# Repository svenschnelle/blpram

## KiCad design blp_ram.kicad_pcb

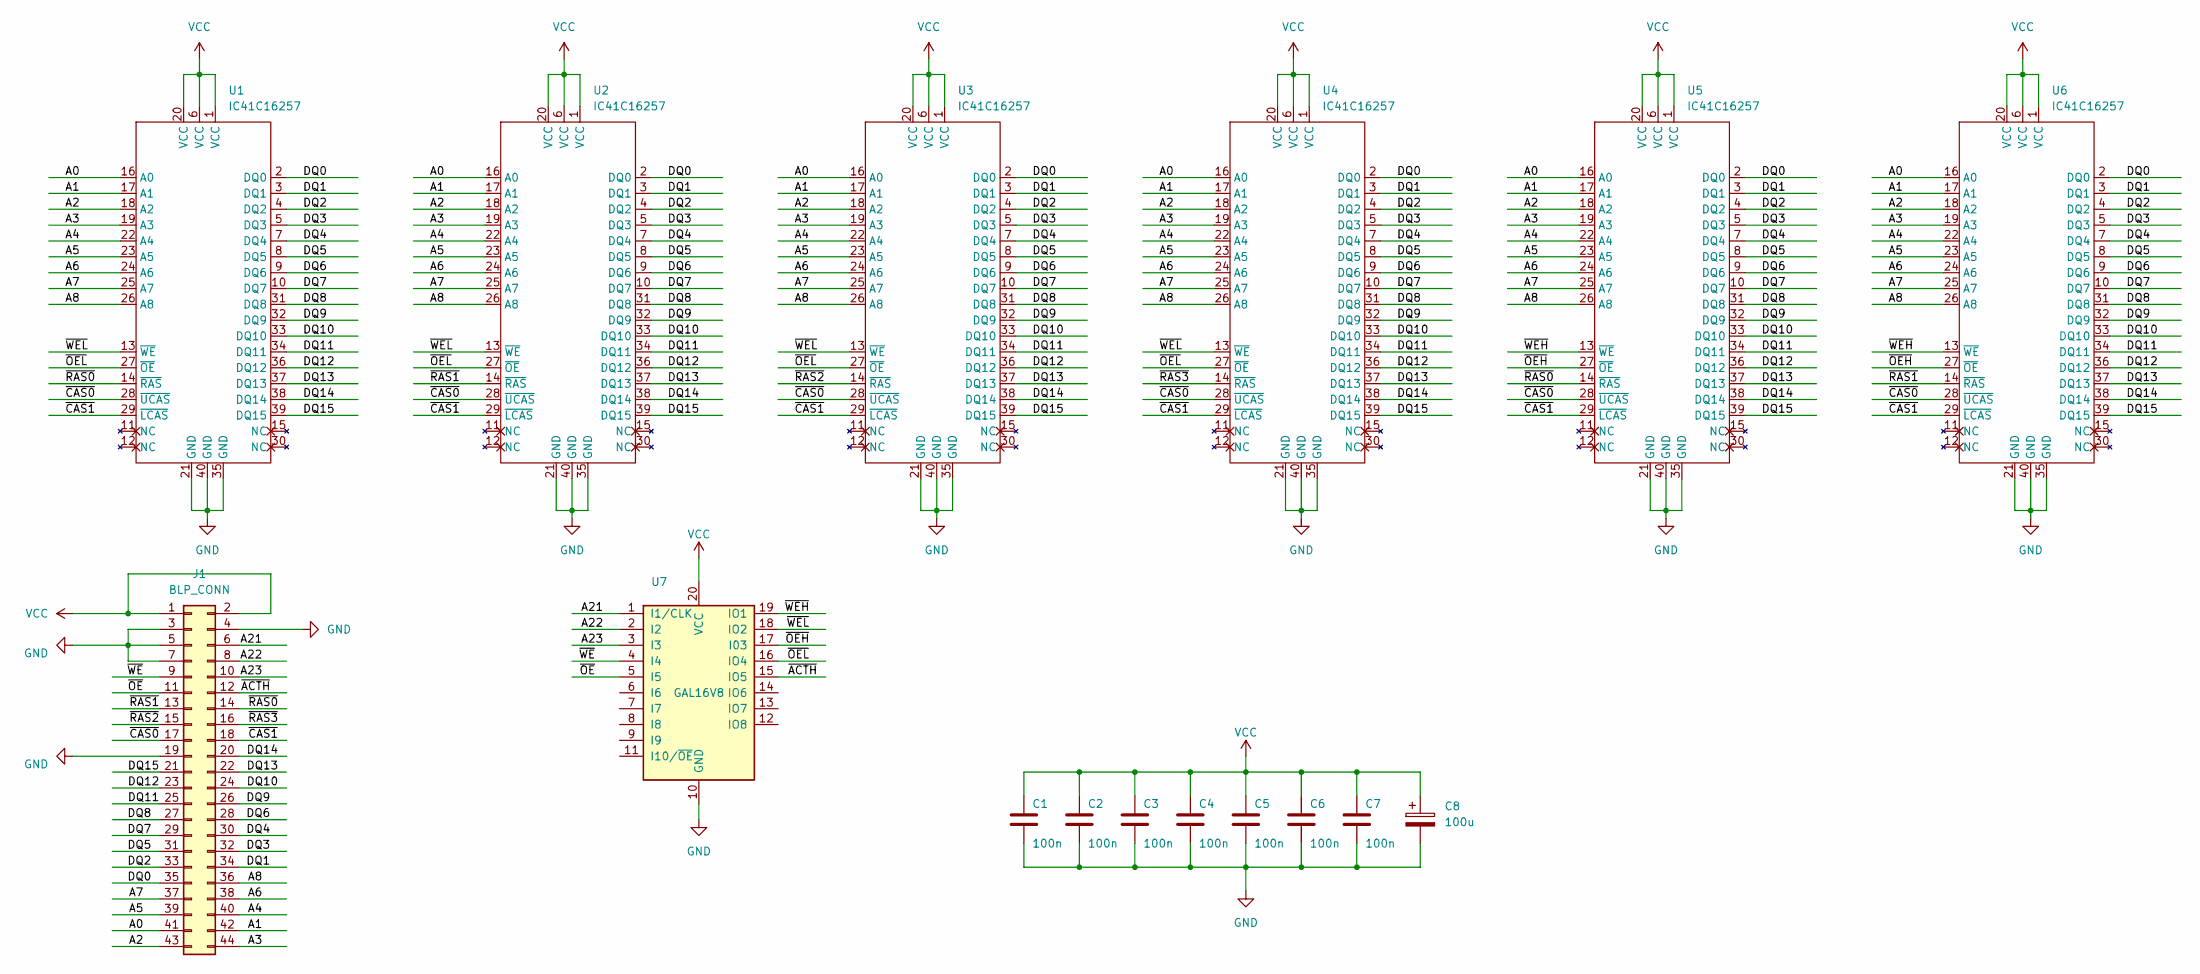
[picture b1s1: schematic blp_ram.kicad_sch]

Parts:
C1, C2, C3, C4, C5, C6, C7: 100n; R_1206_3216Metric_Pad1.30x1.75mm_HandSolder
C8: 100u; CP_Radial_D6.3mm_P2.50mm
J1: BLP_CONN; PinHeader_2x22_P2.54mm_Vertical
U1, U2, U3, U4, U5, U6: IC41C16257; SOJ-40
U7: GAL16V8; DIP-20_W7.62mm

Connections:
/A0: J1.41, U1.16 (A0), U2.16 (A0), U3.16 (A0), U4.16 (A0), U5.16 (A0), U6.16 (A0)
/A1: J1.42, U1.17 (A1), U2.17 (A1), U3.17 (A1), U4.17 (A1), U5.17 (A1), U6.17 (A1)
/A2: J1.43, U1.18 (A2), U2.18 (A2), U3.18 (A2), U4.18 (A2), U5.18 (A2), U6.18 (A2)
/A3: J1.44, U1.19 (A3), U2.19 (A3), U3.19 (A3), U4.19 (A3), U5.19 (A3), U6.19 (A3)
/A4: J1.40, U1.22 (A4), U2.22 (A4), U3.22 (A4), U4.22 (A4), U5.22 (A4), U6.22 (A4)
/A5: J1.39, U1.23 (A5), U2.23 (A5), U3.23 (A5), U4.23 (A5), U5.23 (A5), U6.23 (A5)
/A6: J1.38, U1.24 (A6), U2.24 (A6), U3.24 (A6), U4.24 (A6), U5.24 (A6), U6.24 (A6)
/A7: J1.37, U1.25 (A7), U2.25 (A7), U3.25 (A7), U4.25 (A7), U5.25 (A7), U6.25 (A7)
/A8: J1.36, U1.26 (A8), U2.26 (A8), U3.26 (A8), U4.26 (A8), U5.26 (A8), U6.26 (A8)
/A21: J1.6, U7.1 (I1/CLK)
/A22: J1.8, U7.2 (I2)
/A23: J1.10, U7.3 (I3)
/DQ0: J1.35, U1.2 (DQ0), U2.2 (DQ0), U3.2 (DQ0), U4.2 (DQ0), U5.2 (DQ0), U6.2 (DQ0)
/DQ1: J1.34, U1.3 (DQ1), U2.3 (DQ1), U3.3 (DQ1), U4.3 (DQ1), U5.3 (DQ1), U6.3 (DQ1)
/DQ2: J1.33, U1.4 (DQ2), U2.4 (DQ2), U3.4 (DQ2), U4.4 (DQ2), U5.4 (DQ2), U6.4 (DQ2)
/DQ3: J1.32, U1.5 (DQ3), U2.5 (DQ3), U3.5 (DQ3), U4.5 (DQ3), U5.5 (DQ3), U6.5 (DQ3)
/DQ4: J1.30, U1.7 (DQ4), U2.7 (DQ4), U3.7 (DQ4), U4.7 (DQ4), U5.7 (DQ4), U6.7 (DQ4)
/DQ5: J1.31, U1.8 (DQ5), U2.8 (DQ5), U3.8 (DQ5), U4.8 (DQ5), U5.8 (DQ5), U6.8 (DQ5)
/DQ6: J1.28, U1.9 (DQ6), U2.9 (DQ6), U3.9 (DQ6), U4.9 (DQ6), U5.9 (DQ6), U6.9 (DQ6)
/DQ7: J1.29, U1.10 (DQ7), U2.10 (DQ7), U3.10 (DQ7), U4.10 (DQ7), U5.10 (DQ7), U6.10 (DQ7)
/DQ8: J1.27, U1.31 (DQ8), U2.31 (DQ8), U3.31 (DQ8), U4.31 (DQ8), U5.31 (DQ8), U6.31 (DQ8)
/DQ9: J1.26, U1.32 (DQ9), U2.32 (DQ9), U3.32 (DQ9), U4.32 (DQ9), U5.32 (DQ9), U6.32 (DQ9)
/DQ10: J1.24, U1.33 (DQ10), U2.33 (DQ10), U3.33 (DQ10), U4.33 (DQ10), U5.33 (DQ10), U6.33 (DQ10)
/DQ11: J1.25, U1.34 (DQ11), U2.34 (DQ11), U3.34 (DQ11), U4.34 (DQ11), U5.34 (DQ11), U6.34 (DQ11)
/DQ12: J1.23, U1.36 (DQ12), U2.36 (DQ12), U3.36 (DQ12), U4.36 (DQ12), U5.36 (DQ12), U6.36 (DQ12)
/DQ13: J1.22, U1.37 (DQ13), U2.37 (DQ13), U3.37 (DQ13), U4.37 (DQ13), U5.37 (DQ13), U6.37 (DQ13)
/DQ14: J1.20, U1.38 (DQ14), U2.38 (DQ14), U3.38 (DQ14), U4.38 (DQ14), U5.38 (DQ14), U6.38 (DQ14)
/DQ15: J1.21, U1.39 (DQ15), U2.39 (DQ15), U3.39 (DQ15), U4.39 (DQ15), U5.39 (DQ15), U6.39 (DQ15)
/~ACTH: J1.12, U7.15 (IO5)
/~CAS0: J1.17, U1.28 (~UCAS), U2.28 (~UCAS), U3.28 (~UCAS), U4.28 (~UCAS), U5.28 (~UCAS), U6.28 (~UCAS)
/~CAS1: J1.18, U1.29 (~LCAS), U2.29 (~LCAS), U3.29 (~LCAS), U4.29 (~LCAS), U5.29 (~LCAS), U6.29 (~LCAS)
/~OEH: U5.27 (~OE), U6.27 (~OE), U7.17 (I03)
/~OEL: U1.27 (~OE), U2.27 (~OE), U3.27 (~OE), U4.27 (~OE), U7.16 (IO4)
/~OE: J1.11, U7.5 (I5)
/~RAS0: J1.14, U1.14 (~RAS), U5.14 (~RAS)
/~RAS1: J1.13, U2.14 (~RAS), U6.14 (~RAS)
/~RAS2: J1.15, U3.14 (~RAS)
/~RAS3: J1.16, U4.14 (~RAS)
/~WEH: U5.13 (~WE), U6.13 (~WE), U7.19 (IO1)
/~WEL: U1.13 (~WE), U2.13 (~WE), U3.13 (~WE), U4.13 (~WE), U7.18 (IO2)
/~WE: J1.9, U7.4 (I4)
GND: C1.2, C2.2, C3.2, C4.2, C5.2, C6.2, C7.2, C8.2, J1.3, J1.4, J1.5, J1.7, J1.19, U1.21 (GND), U1.35 (GND), U1.40 (GND), U2.21 (GND), U2.35 (GND), U2.40 (GND), U3.21 (GND), U3.35 (GND), U3.40 (GND), U4.21 (GND), U4.35 (GND), U4.40 (GND), U5.21 (GND), U5.35 (GND), U5.40 (GND), U6.21 (GND), U6.35 (GND), U6.40 (GND), U7.10 (GND)
VCC: C1.1, C2.1, C3.1, C4.1, C5.1, C6.1, C7.1, C8.1, J1.1, J1.2, U1.1 (VCC), U1.6 (VCC), U1.20 (VCC), U2.1 (VCC), U2.6 (VCC), U2.20 (VCC), U3.1 (VCC), U3.6 (VCC), U3.20 (VCC), U4.1 (VCC), U4.6 (VCC), U4.20 (VCC), U5.1 (VCC), U5.6 (VCC), U5.20 (VCC), U6.1 (VCC), U6.6 (VCC), U6.20 (VCC), U7.20 (VCC)

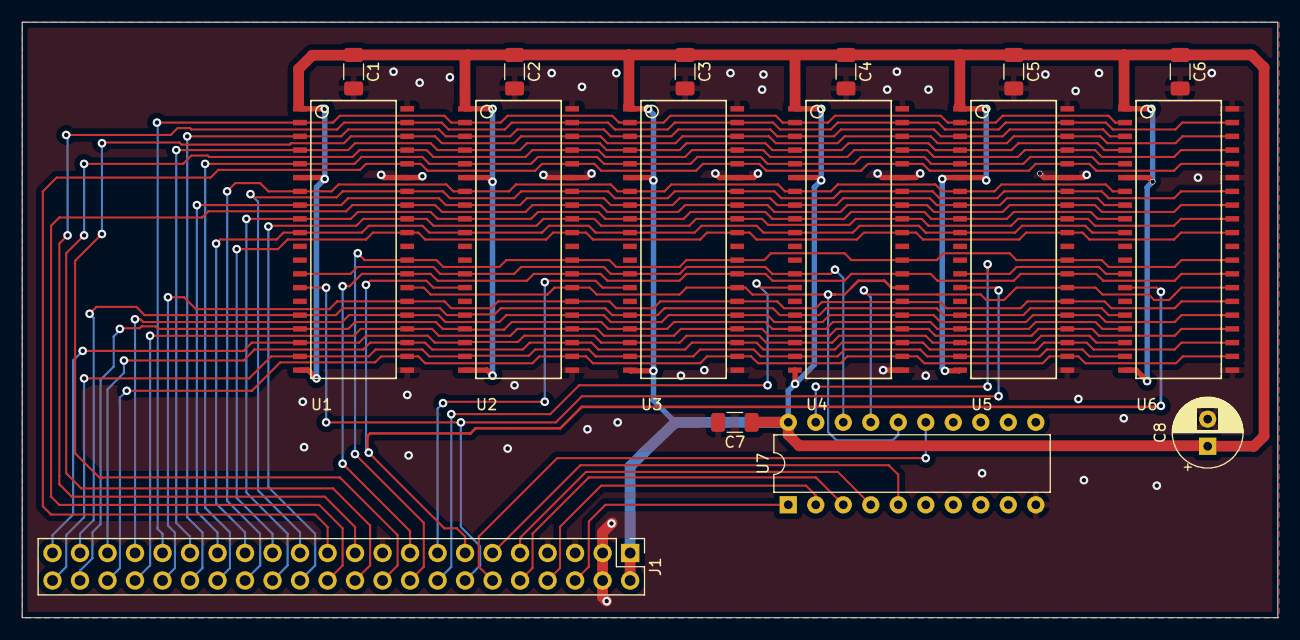
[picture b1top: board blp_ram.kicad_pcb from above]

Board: 2 copper layers, 116.0 x 55.0 mm, 16 parts (0 on the bottom side), 43 nets.

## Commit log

2022-04-19 Add HW design files
2022-04-19 add GAL design files
    use PALASM to translate
